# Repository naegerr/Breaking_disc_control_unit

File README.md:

# Breaking_disc_control_unit
BDA

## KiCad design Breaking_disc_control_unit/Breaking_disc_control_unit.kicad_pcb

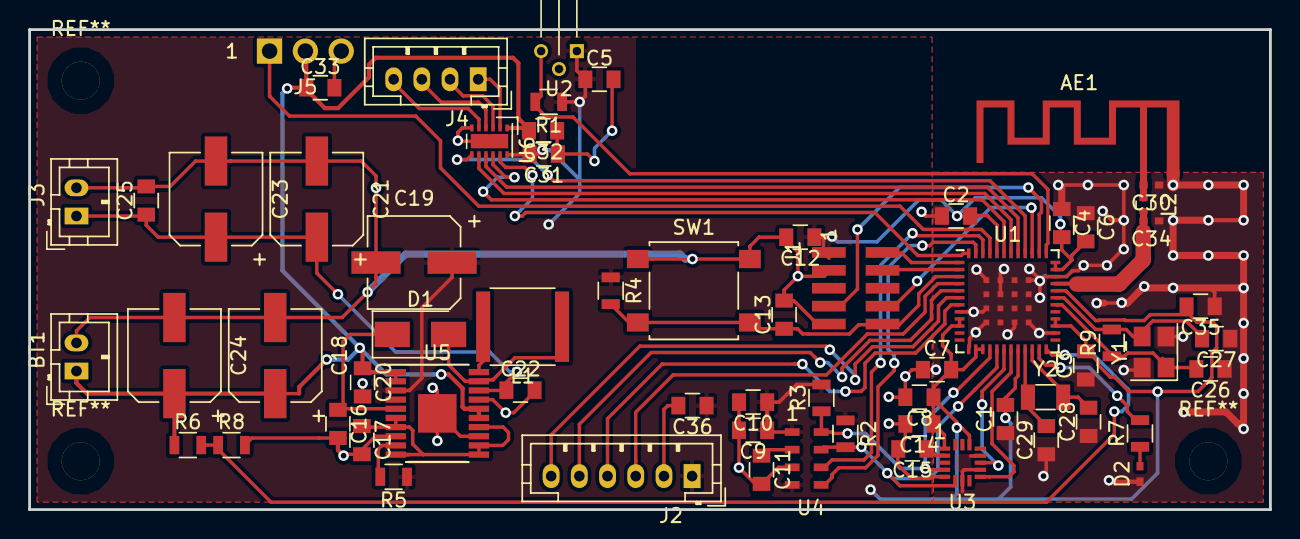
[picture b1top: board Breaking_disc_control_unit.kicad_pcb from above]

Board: 2 copper layers, 88.0 x 34.0 mm, 65 parts (0 on the bottom side), 46 nets.

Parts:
AE1: MIFA; Texas_SWRA117D_2.4GHz_Left
BT1: 3.7V LiPo; JST_PH_B2B-PH-K_02x2.00mm_Straight
C1, C2, C3, C5, C7, C9, C11, C12, C13, C14, C15, C17, C25, C31, C32, C33, C36: 100n; C_0805
C4, C6, C26, C27, C35: 10p; C_0805
C8, C16: 4u7; C_0805
C10: 10u; C_0805
C18, C21: 47u; CP_Elec_6.3x5.8
C19, C23, C24: 100u; CP_Elec_6.3x5.8
C20, C22: 1u; C_0805
C28, C29: 18p; C_0805
C30, C34: 0.7pF; C_0402_NoSilk
D1: D_Schottky; D_SMA
D2: LED; C_0402_NoSilk
J1: Conn_02x05_Odd_Even; Header_2x5_1.27
J2: Conn_02x03_Odd_Even; JST_PH_B6B-PH-K_06x2.00mm_Straight
J3: Conn_01x02; JST_PH_B2B-PH-K_02x2.00mm_Straight
J4: Conn_01x04; JST_PH_B4B-PH-K_04x2.00mm_Straight
J5: Conn_01x03; Header_1x3_2.54
L1: 22u; C_2220
L2: 5.1nH; L_0402
R1, R2, R3: 47k; R_0805
R4: 100k; R_0805
R5, R9: 1M; R_0805
R6: 2.2M; R_0805
R7: 1k8; R_0805
R8: 4.7M; R_0805
SW1: SW_Push; SW_SPST_B3S-1000
U1: MKW31Z256VHT4; bdcu_QFN-48-1EP_7x7mm_Pitch0.5mm
U2: TLV4964; TO-92_Horizontal1_Molded_Narrow
U3: MMA8452Q; QFN_16_MMA8452QT
U4: MPL3115A2; FP_MPL3115
U5: LTC3106; LTC3106_TSSOP-20_4.4x6.5mm_Pitch0.65mm
U6: DRV8835; WSON-12-1EP_3x2mm_Pitch0.5mm
Y1: Crystal_GND24; Crystal_SMD_Abracon_ABM8G-4pin_3.2x2.5mm
Y2: 32,768KHz; Crystal_SMD_3215-2pin_3.2x1.5mm

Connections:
+3V3: C1.2, C2.2, C3.2, C4.2, C5.1, C6.2, C7.2, C8.1, C9.1, C10.1, C12.1, C14.1, C19.1, C31.2, C35.2, C36.1, J1.1, J2.1, R1.1, R2.1, R3.2, R4.1, R5.1, U1.9, U1.10, U1.14, U1.15, U1.20, U1.27, U1.28, U1.32, U1.35, U1.36, U1.44, U2.1, U3.1, U3.14, U4.1, U4.4, U5.3, U6.12
+BATT: BT1.1, C18.1, C20.1, C24.1, C32.2, C33.1, J5.2, R6.1, U5.1, U5.2, U5.15, U5.16, U6.1
EXTAL_32KHZ: C29.2, U1.21, Y2.2
EXTAL_32MHZ: C26.2, R9.1, U1.30, Y1.1
GND: AE1.2, BT1.2, C1.1, C2.1, C3.1, C4.1, C5.2, C6.1, C7.1, C8.2, C9.2, C10.2, C11.2, C12.2, C13.2, C14.2, C15.2, C16.2, C17.2, C18.2, C19.2, C20.2, C21.2, C22.2, C23.2, C24.2, C25.2, C26.1, C27.1, C28.1, C29.1, C30.1, C31.1, C32.1, C33.2, C34.1, C35.1, C36.2, D2.1, J1.3, J1.9, J2.2, J3.2, J5.3, R8.2, SW1.1, U1.8, U1.13, U1.26, U1.34, U1.49, U1.50, U1.51, U1.52, U1.53, U1.54, U1.55, U1.56, U1.57, U1.58, U1.59, U1.60, U1.61, U1.62, U1.63, U1.64, U2.2, U3.5, U3.7, U3.10, U3.12, U4.3, U5.8, U5.13, U5.17, U5.21, U6.6, U6.13, Y1.2, Y1.4
HALL_OUT: R1.2, U1.37, U2.3
I2C_INT_11: U1.18, U3.11
I2C_INT_12: U1.19, U3.9
I2C_INT_21: U1.46, U4.6
I2C_INT_22: U1.47, U4.5
I2C_SCL: R3.1, U1.16, U3.4, U4.8
I2C_SDA: R2.2, U1.17, U3.6, U4.7
LED: R7.2, U1.23
unnamed: AE1.1, C30.2, L2.1
unnamed: C11.1, U4.2
unnamed: C15.1, U3.2
unnamed: C16.1, D1.1, U5.5
unnamed: C17.1, U5.6, U5.7, U5.10, U5.11, U5.12, U5.14
unnamed: C34.2, L2.2, U1.33
unnamed: D1.2, L1.1, U5.19
unnamed: D2.2, R7.1
unnamed: J4.1, U6.2
unnamed: J4.2, U6.3
unnamed: J4.3, U6.4
unnamed: J4.4, U6.5
unnamed: L1.2, U5.20
unnamed: R5.2, U5.9
unnamed: R6.2, R8.1, U1.24
PWM_SERVO: J5.1, U1.45
RESET: C13.1, J1.10, R4.2, SW1.2, U1.3
SM_AIN1/AP: U1.43, U6.10
SM_AIN2/AENBL: U1.41, U6.9
SM_BIN1/BP: U1.42, U6.8
SM_BIN2/BENBL: U1.40, U6.7
SM_MODE: U1.48, U6.11
SPI1_PCS0_EXT: J2.4, U1.7
SPI1_SCK_EXT: J2.6, U1.6
SPI1_SIN_EXT: J2.5, U1.5
SPI1_SOUT_EXT: J2.3, U1.4
SWD_CLK: J1.4, U1.2
SWD_DIO: J1.2, U1.1
UART0_RX: J1.7, U1.38
UART0_TX: J1.8, U1.39
VSOURCE: C21.1, C22.1, C23.1, C25.1, J3.1, U5.18
XTAL_32KHZ: C28.2, U1.22, Y2.1
XTAL_32MHZ: C27.2, R9.2, U1.31, Y1.3

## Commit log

2017-10-18 Init
2017-10-20 Library erstellt
2017-10-20 MIt Library
2017-10-22 Acceleration sensor, altimeter, Debug interface
2017-10-23 LTC3106 start, some configs of MKW31Z
2017-10-24 LTC3106 testing with LTSPICE -> inserted infos(ESR,etc.)
2017-10-26 LTC3106 fertig with 0.37 to 6V -> NOT reviewed
2017-10-28 Antenna, Quarz done
2017-10-30 Schema fertig. Bis auf Powerbeschaltung von MKW31Z. Version mit LTC3106
2017-10-30 Schematic finished and verified by me!
2017-10-31 Schematic modified -> L =22 uH because more efficient in lower voltages. Footprints set
2017-11-01 3D library
2017-11-01 Revert "3D library"
    This reverts commit e9ddbec3ae18a37024c3ab9a6ee9566cfe905b0c.
2017-11-01 Footprints modified
2017-11-02 Footprints adapted
2017-11-02 Footprints addes and Antenna matching realized
2017-11-04 Direction of signal set. Start Layouting
2017-11-05 Layout Anordnung
2017-11-06 ADC to Battery added -> UV of Battery is disabled because battery directly connected to Actuaturs.
2017-11-06 ADC added
2017-11-08 Diode for ADC added
2017-11-08 Changed Antenna -> Must be matched after measuring and started layouting
2017-11-08 some tracks
2017-11-09 Layout fast fertig!
2017-11-11 LAYOUT FERTIG!!! NOT REVIEWED YET!
2017-11-11 LAYOUT REVIEWD AND SENT!
2017-11-12 BOM new generated
2017-11-12 renamed MCU, and BOM erstellt
2017-11-13 Bohrlöcher in Drillfile eingefügt und angepasst
2017-11-13 Copper pour modified
2017-11-13 Gerberfiles HSLU
2017-11-13 update und Outline angepasst
2017-11-15 renamed once more
2017-11-15 no message
2017-11-15 sadf
2017-11-20 Library new created
2017-11-20 rule check!
2017-12-10 Information added from component
2017-12-11 some pdf erstellt
2017-12-27 V1.1 Schematic
2018-01-03 NOthing
2018-01-05 Z-Diode added!
